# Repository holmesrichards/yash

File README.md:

# YASH

This is a Kosmo format version of René Schmitz's [YASH](https://www.schmitzbits.de/sah.html) sample and hold synth module.

The circuit is pretty much as Schmitz designed it. The only significant changes are the addition of an output jack for the clock signal, an attenuator for the input signal, and a switch to bypass the capacitor on the clock input. The latter turns the module from a sample and hold into a track and hold: applying a gate to the clock input causes the output to track the input voltage, and then when the gate turns off the last output voltage is held until the next gate.

## Current draw
11.3 mA +12 V, 4.0 mA -12 V

## Photos

## Documentation

* [Schematic](Docs/yash.pdf)
* PCB layout: [front](Docs/yash_layout_front.pdf), [back](Docs/yash_layout_back.pdf)
* [BOM](Docs/yash_bom.md)
* [Build notes](Docs/build.md)
* [Blog post](https://analogoutputblog.wordpress.com/2022/05/06/yet-another-sample-and-hold/)

## GitHub repository

* [https://github.com/holmesrichards/yash](https://github.com/holmesrichards/yash)

## Submodules

This repo uses submodules aoKicad and Kosmo_panel, which provide needed libaries for KiCad. To clone:

```
git clone git@github.com:holmesrichards/yash.git
git submodule init
git submodule update
```

Alternatively do

```
git clone --recurse-submodules git@github.com:holmesrichards/yash.git
```

Or if you download the repository as a zip file, you must also click on the "aoKicad" and "Kosmo\_panel" links on the GitHub page (they'll have "@ something" after them) and download them as separate zip files which you can unzip into this repo's aoKicad and Kosmo\_panel directories.

If desired, copy the files from aoKicad and Kosmo\_panel to wherever you prefer (your KiCad user library directory, for instance, if you have one). Then in KiCad, go into Edit Symbols and add symbol libraries 

```
aoKicad/ao_symbols
Kosmo_panel/Kosmo
```
and go into Edit Footprints and add footprint libraries 
```
aoKicad/ao_tht
Kosmo_panel/Kosmo_panel.
```

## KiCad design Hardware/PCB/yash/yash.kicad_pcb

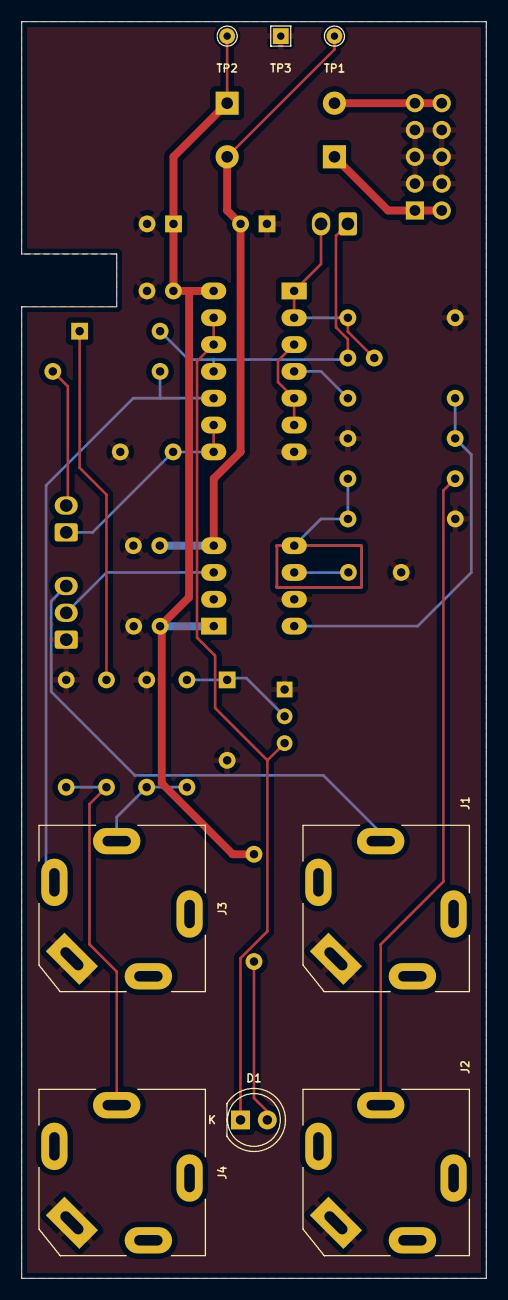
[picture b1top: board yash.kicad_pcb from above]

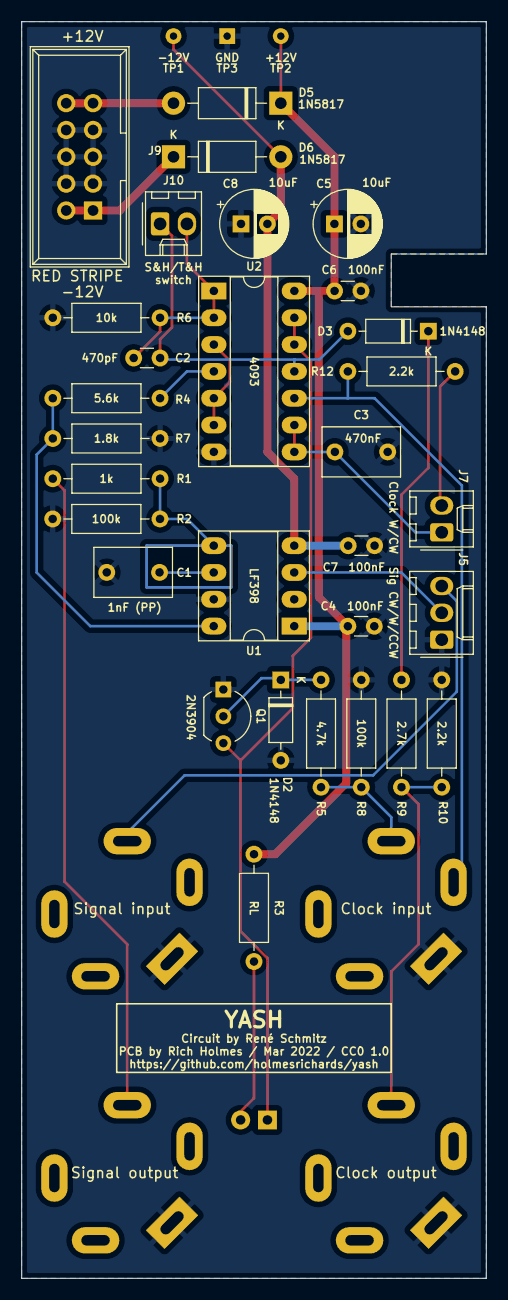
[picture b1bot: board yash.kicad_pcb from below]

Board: 2 copper layers, 44.0 x 119.0 mm, 39 parts (30 on the bottom side), 24 nets.

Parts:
C1: 1nF (PP); C_Rect_L7.2mm_W4.5mm_P5.00mm_FKS2_FKP2_MKS2_MKP2
C2: 470pF; C_Disc_D3.0mm_W1.6mm_P2.50mm
C3: 470nF; C_Rect_L7.2mm_W4.5mm_P5.00mm_FKS2_FKP2_MKS2_MKP2
C4, C6, C7: 100nF; C_Disc_D3.0mm_W1.6mm_P2.50mm
C5, C8: 10uF; CP_Radial_D6.3mm_P2.50mm
D1: LED_green; LED_D5.0mm
D2, D3: 1N4148; D_DO-35_SOD27_P7.62mm_Horizontal
D5, D6: 1N5817; D_DO-41_SOD81_P10.16mm_Horizontal
GRAF1: Holes; yash_panel_holes
J1, J2, J4: AudioJack2; Jack_6.35mm_PJ_629HAN_slots
J3: AudioJack2_SwitchT; Jack_6.35mm_PJ_629HAN_slots
J5: 3_pin_Molex_header; Molex_KK-254_AE-6410-03A_1x03_P2.54mm_Vertical
J7, J10: 2_pin_Molex_header; Molex_KK-254_AE-6410-02A_1x02_P2.54mm_Vertical
J9: Synth_power_2x5; Power_Header
Q1: 2N3904; TO-92_Inline_Wide
R1: 1k; R_Axial_DIN0207_L6.3mm_D2.5mm_P10.16mm_Horizontal
R2, R8: 100k; R_Axial_DIN0207_L6.3mm_D2.5mm_P10.16mm_Horizontal
R3: RL; R_Axial_DIN0207_L6.3mm_D2.5mm_P10.16mm_Horizontal
R4: 5.6k; R_Axial_DIN0207_L6.3mm_D2.5mm_P10.16mm_Horizontal
R5: 4.7k; R_Axial_DIN0207_L6.3mm_D2.5mm_P10.16mm_Horizontal
R6: 10k; R_Axial_DIN0207_L6.3mm_D2.5mm_P10.16mm_Horizontal
R7: 1.8k; R_Axial_DIN0207_L6.3mm_D2.5mm_P10.16mm_Horizontal
R9: 2.7k; R_Axial_DIN0207_L6.3mm_D2.5mm_P10.16mm_Horizontal
R10, R12: 2.2k; R_Axial_DIN0207_L6.3mm_D2.5mm_P10.16mm_Horizontal
TP1: -12V; TestPoint_THTPad_D1.5mm_Drill0.7mm
TP2: +12V; TestPoint_THTPad_D1.5mm_Drill0.7mm
TP3: GND; TestPoint_THTPad_1.5x1.5mm_Drill0.7mm
U1: LF398; DIP-8_W7.62mm_Socket_LongPads
U2: 4093; DIP-14_W7.62mm_Socket_LongPads

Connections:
+12V: C4.1, C5.1, C6.1, D5.1 (K), R3.1, TP2.1, U1.1 (V+), U2.14 (VCC)
-12V: C7.2, C8.2, D6.2 (A), TP1.1, U1.4 (V-)
/+12_IN: D5.2 (A), J9.9 (+12V), J9.10 (+12V)
/-12_IN: D6.1 (K), J9.1 (-12V), J9.2 (-12V)
/CLOCK_INPUT: J3.T, R5.1, R8.1
/CLOCK_OUTPUT: J4.T, R9.2, R10.1
/OUT398: R1.1, R2.1, U1.5 (OUTPUT)
/SIGNAL_OUTPUT: J2.T, R1.2
CLKFR_CW: C3.1, J7.1, U2.8, U2.9
CLKFR_W: J7.2, R12.1
GND: C1.2, C3.2, C4.2, C5.2, C6.2, C7.1, C8.1, D2.2 (A), J1.S, J2.S, J3.S, J4.S, J5.1, J9.3 (GND), J9.4 (GND), J9.5 (GND), J9.6 (GND), J9.7 (GND), J9.8 (GND), Q1.1 (E), R2.2, R6.2, R7.2, R8.2, R10.2, TP3.1, U1.7 (LOG_REF), U2.7 (GND)
unnamed: C1.1, U1.6 (C_H)
unnamed: D1.1 (K), Q1.3 (C), U2.12, U2.13
unnamed: D1.2 (A), R3.2
unnamed: D2.1 (K), Q1.2 (B), R5.2
unnamed: D3.1 (K), R9.1
unnamed: J3.TN, R12.2, U2.10
unnamed: R4.1, U2.4
unnamed: R4.2, R7.1, U1.8 (LOGIC)
unnamed: U2.3, U2.5, U2.6
SIGLVL_CW: J1.T, J5.3
SIGLVL_W: J5.2, U1.3 (INPUT)
TH_1: C2.1, D3.2 (A), J10.1, U2.11
TH_2: C2.2, J10.2, R6.1, U2.1, U2.2

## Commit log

2022-03-27 Initial version
2022-03-27 Libraries
2022-04-03 README, panel and PCB tweaks
2022-04-24 Gerbers
2022-04-24 Redo guard ring as redundant tracks
2022-05-06 CW not CCW, put LED on correct side of PCB
2022-05-06 Post fab updates
2022-05-06 aoKicad
2022-05-06 LICENSE
2022-05-06 Explain "RL"
2022-05-23 Current draw

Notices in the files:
Hardware/PCB/yash/yash.kicad_pcb:
PCB by Rich Holmes / Mar 2022 / CC0 1.0
